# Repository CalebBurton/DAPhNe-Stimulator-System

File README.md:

## Digitally Adjustable Phrenic Nerve (DAPhNe) Stimulator System
### Northwestern University BME Senior Capstone Design (2016-2017)
#### Center for Autonomic Medicine in Pediatrics (CAMP) at Ann & Robert H. Lurie Children's Hospital of Chicago

<br></br>

Most recent documentation:

[**Digitally Adjustable Phrenic Nerve (DAPhNe) Stimulator - Getting Started, Rev 1.0**](https://github.com/AlexeyRevinski/DAPhNe-Stimulator-System/blob/master/Reference%20Documentation/DAPhNe_Getting_Started_v_1_0.pdf)

[**Digitally Adjustable Phrenic Nerve (DAPhNe) Stimulator - Technical Reference, Rev 1.1**](https://github.com/AlexeyRevinski/DAPhNe-Stimulator-System/blob/master/Reference%20Documentation/DAPhNe_Technical_Reference_v_1_1.pdf)

<br></br>

The focus of this project is the development and testing of a novel implantable phrenic nerve stimulator, to be used in patients with Congenital Central Hypoventilation Syndrome (CCHS) - specifically, children. The following sections summarize the project; to get to know the project in extensive detail, please refer to project documents under "Reference Documentation".

<br></br>

## Project Description
### Introduction to CCHS
Patients with CCHS have diminished autonomic nervous system function, which results in a variety of symptoms, the most prominent of which is insufficient ventilation. This results from poor phrenic nerve conduction; phrenic nerve is responsible for stimulating diaphragmatic contractions. While some patients are affected only mildly, some cannot breathe on their own, and require 24/7 ventilatory support.

### Current Solutions
This is usually done with a mechanical positive pressure ventilator; oxygenated air is forced into the patient's lungs by a mechanical piston. While this is a proven solution to the problem, these devices are enormous to carry around for small children; they are loud and extremely expensive. Patients also require a tracheotomy to be performed for this to work.

Another solution is to stimulate the phrenic nerve electrically. The only device that does this right now is the [**Mark IV stimulator**](http://www.averybiomedical.com/breathing-pacemakers/system-information/) from Avery Biomedical. It consists of an external transmitter that sends pulses inductively through tissue to a passive receiver that interfaces with an electrode in the vicinity of the nerve. This is the only solution on the market, and, while it has several advantages over the mechanical ventilator, it also has a variety of shortcomings that include:
 - Restricted mobility - antennae must be always attached to patient’s body for successful stimulation
 - System does not support multiple activity level settings, so each patient is forced to use two or three transmitters and mechanically switch between them each time the patient participates in a different activity (sleep vs. walk vs. run vs. eat, etc.)
 - Weight and size of the transmitter box - weight = 2 lb, volume = 511 cm3. A small child must carry this weight constantly
 - Unintuitive user interface - the device has non-linear, poorly labeled dials
 - Required presence of the external transmitter close to the patient's body restricts the patient's ability to participate in water-related activities.

### DAPhNe Stimulator System
The Digitally Adjustable Phrenic Nerve (DAPhNe) Stimulator System aims to lift those drawbacks and provide children with CCHS an implantable stimulator that would eliminate the need to be tethered to an external controller, allow for a variety of programmable settings to be switched "on the fly", and allow participation on water-related activities without fear of device malfunction or electric shock. 

The above objectives are accomplished by digitalization of the system, employing wireless charging, and wireless short range communication.  The DAPhNe stimulator is battery powered and charged inductively through skin; it provides constant stimulation to the nerve on its own without the need for an external inductive antenna. The external controller uses NFC technology to wirelessly transmit new activity level parameters to the implant, and the implant automatically adjusts its internal variables on the next breath. Thus, the patient is not tethered to anything, and the transition between various activity levels is seamless. Based on most recent power consumption testing and calculations, the device in its current state would be able to support the patient for one week on one battery charge, after which the battery is recharged wirelessly.

Currently, the DAPhNe Stimulator System consists of two custom-designed PCB prototype boards interfacing with some off-the-shelf components. This prototype was recently tested for equivalence against the Avery Biomedical Mark IV system in New Zealand white rabbits, and proved successful in stimulating the phrenic nerve effectively. The external user interface is being developed concurrently. 
<br></br>

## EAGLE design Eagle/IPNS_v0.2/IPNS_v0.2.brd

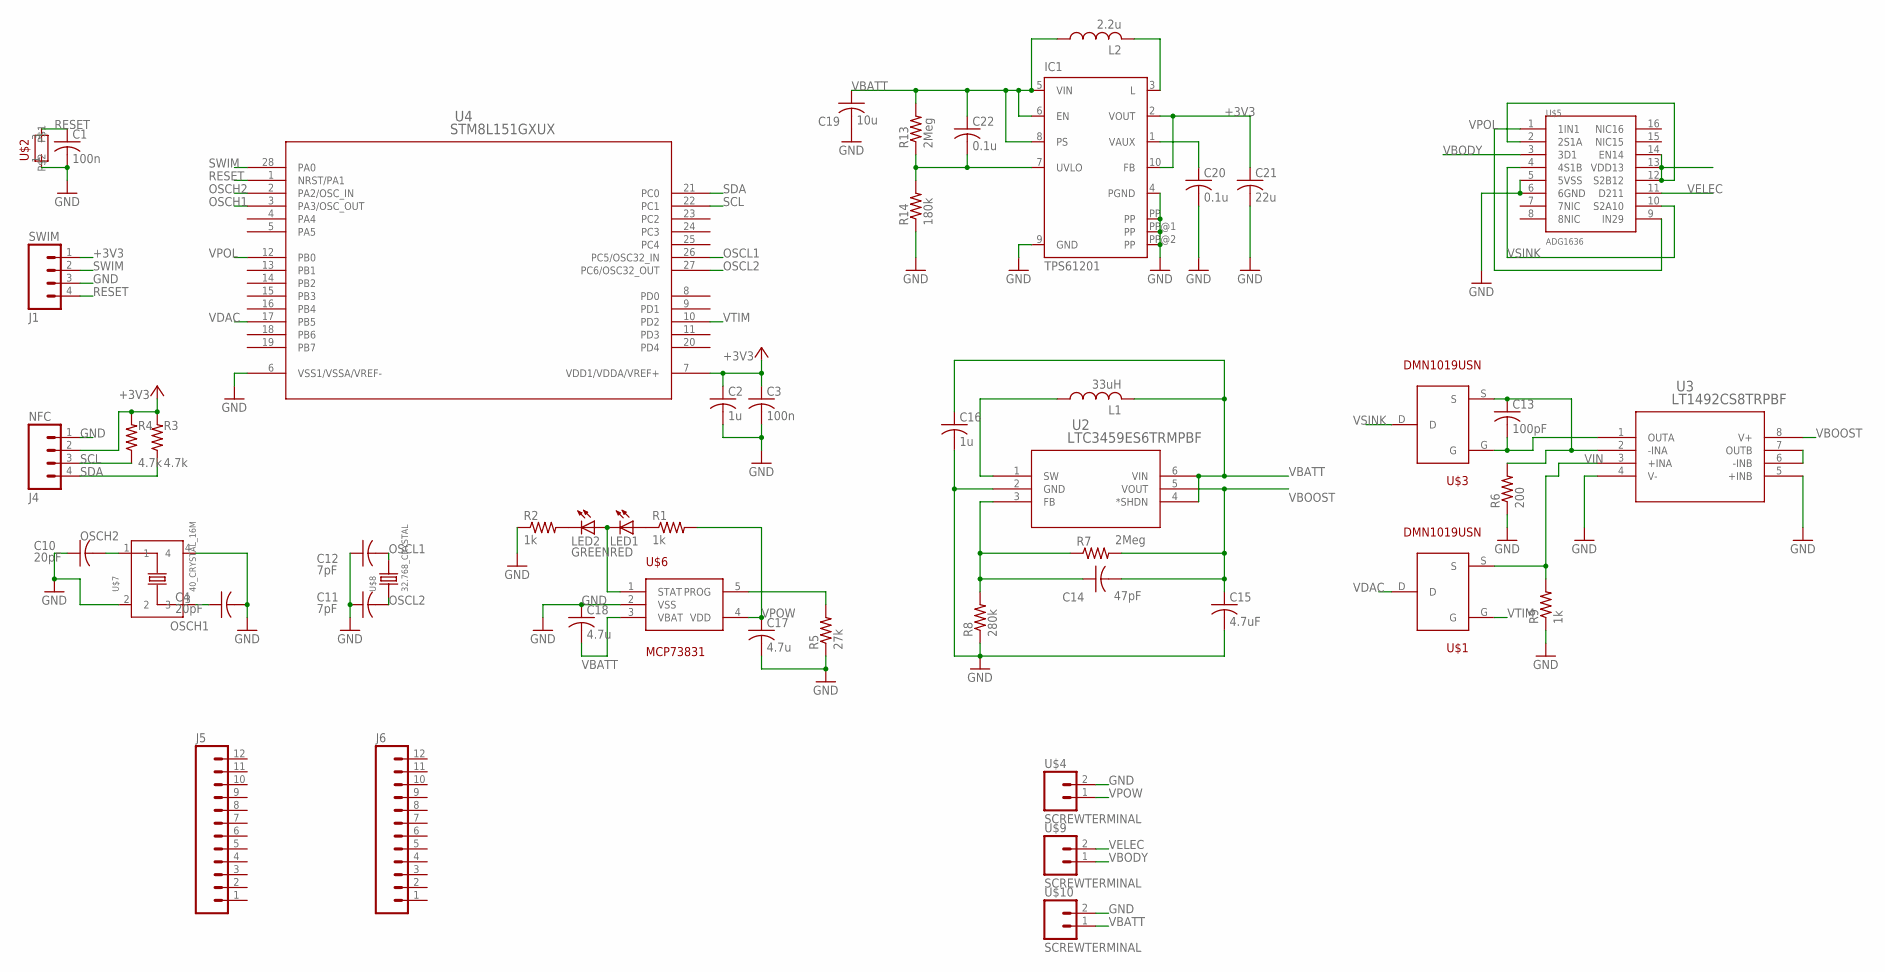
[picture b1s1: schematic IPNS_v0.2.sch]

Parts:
C1, C3: 100n; C0603
C2, C16: 1u; C0603
C4, C10: 20pF; C0603
C11, C12: 7pF; C0603
C13: 100pF; C0603
C14: 47pF; C0603
C15: 4.7uF; C0603
C17, C18: 4.7u; C0603
C19: 10u; C0603
C20, C22: 0.1u; C0603
C21: 22u; C0603
IC1: TPS61201; S-PDSO-N10
J1: SWIM; 1X04
J4: NFC; 1X04
J5, J6: M12PTH; 1X12
L1: 33uH; L2012C
L2: 2.2u; L2012C
LED1: RED; SML0603
LED2: GREEN; SML0603
R1, R2, R9: 1k; R0603
R3, R4: 4.7k; R0603
R5: 27k; R0603
R6: 200; R0603
R7, R13: 2Meg; R0603
R8: 280k; R0603
R14: 180k; R0603
U2: LTC3459ES6TRMPBF; TSOT-23_S6
U3: LT1492CS8TRPBF; SO-8_S
U4: STM8L151GXUX; UFQFPN-28
U$1, U$3: DMN1019USN
U$2: PUSH-BUTTON
U$4, U$9, U$10: SCREWTERMINAL
U$5: ADG1636; TSSOP16
U$6: MCP78381; SOT23-5L
U$7: 40_CRYSTAL_16M; X4-SMD-3.2X2.5X0.7MM
U$8: 32.768_CRYSTAL; X2-SMD-3.2X1.5X0.55MM

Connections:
+3V3: C2.1, C3.1, C21.1, IC1.2 (VOUT), IC1.10 (FB), J1.1, J4.2, R3.2, R4.2, U4.7 (VDD1/VDDA/VREF+)
GND: C1.2, C2.2, C3.2, C4.2, C10.1, C11.1, C12.1, C15.2, C16.2, C17.2, C18.1, C19.2, C20.2, C21.2, IC1.4 (PGND), IC1.9 (GND), IC1.PP, IC1.PP@1 (PP), IC1.PP@2 (PP), J1.3, J4.1, R2.1, R5.1, R6.1, R8.1, R9.1, R14.1, U2.2 (GND), U3.4 (V-), U3.5 (+INB), U4.6 (VSS1/VSSA/VREF-), U$2.1, U$4.2, U$5.5 (5VSS), U$5.6 (6GND), U$6.2 (VSS), U$7.2, U$7.4, U$10.2
unnamed: LED1.C, LED2.A, U$6.1 (STAT)
unnamed: C13.1, R6.2, U3.2 (-INA), U$3.S
unnamed: U3.6 (-INB), U3.7 (OUTB)
unnamed: C14.1, R7.1, R8.2, U2.3 (FB)
unnamed: L1.1, U2.1 (SW)
unnamed: LED2.C, R2.2
unnamed: LED1.A, R1.1
unnamed: C13.2, U3.1 (OUTA), U$3.G
unnamed: R5.2, U$6.5 (PROG)
unnamed: IC1.3 (L), L2.2
unnamed: C20.1, IC1.1 (VAUX)
unnamed: C22.2, IC1.7 (UVLO), R13.1, R14.2
unnamed: U$5.2 (2S1A), U$5.12 (S2B12), U$5.13 (VDD13), U$5.14 (EN14)
OSCH1: C4.1, U4.3 (PA3/OSC_OUT), U$7.3
OSCH2: C10.2, U4.2 (PA2/OSC_IN), U$7.1
OSCL1: C12.2, U4.26 (PC5/OSC32_IN), U$8.2
OSCL2: C11.2, U4.27 (PC6/OSC32_OUT), U$8.1
RESET: C1.1, J1.4, U4.1 (NRST/PA1), U$2.3
SCL: J4.3, R4.1, U4.22 (PC1)
SDA: J4.4, R3.1, U4.21 (PC0)
SWIM: J1.2, U4.28 (PA0)
VBATT: C16.1, C18.2, C19.1, C22.1, IC1.5 (VIN), IC1.6 (EN), IC1.8 (PS), L1.2, L2.1, R13.2, U2.4 (*SHDN), U2.6 (VIN), U$6.3 (VBAT), U$10.1
VBODY: U$5.3 (3D1), U$9.1
VBOOST: C14.2, C15.1, R7.2, U2.5 (VOUT), U3.8 (V+)
VDAC: U4.17 (PB5), U$1.D
VELEC: U$5.11 (D211), U$9.2
VIN: R9.2, U3.3 (+INA), U$1.S
VPOL: U4.12 (PB0), U$5.1 (1IN1), U$5.9 (IN29)
VPOW: C17.1, R1.2, U$4.1, U$6.4 (VDD)
VSINK: U$3.D, U$5.4 (4S1B), U$5.10 (S2A10)
VTIM: U4.10 (PD2), U$1.G

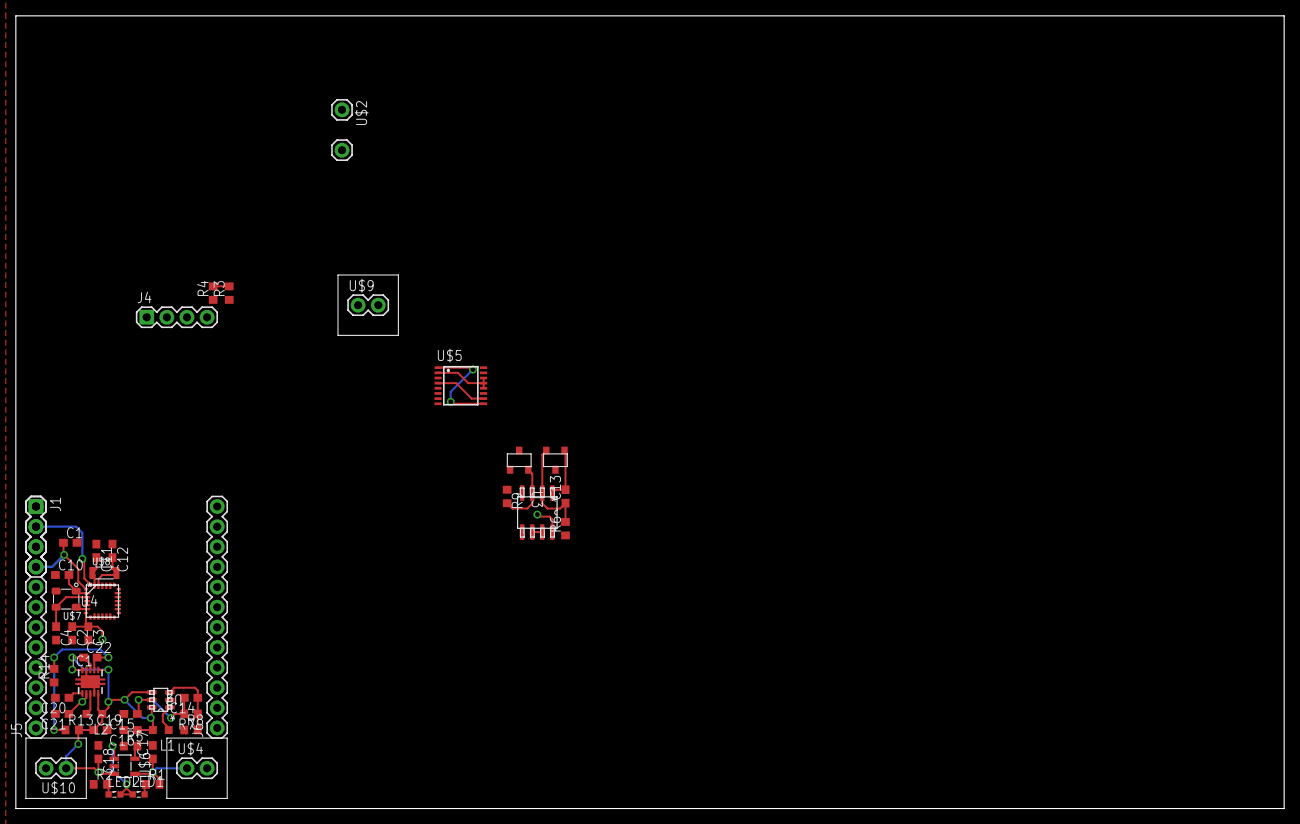
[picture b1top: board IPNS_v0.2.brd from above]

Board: 2 copper layers, 160.0 x 100.0 mm, 50 parts (0 on the bottom side), 33 nets.

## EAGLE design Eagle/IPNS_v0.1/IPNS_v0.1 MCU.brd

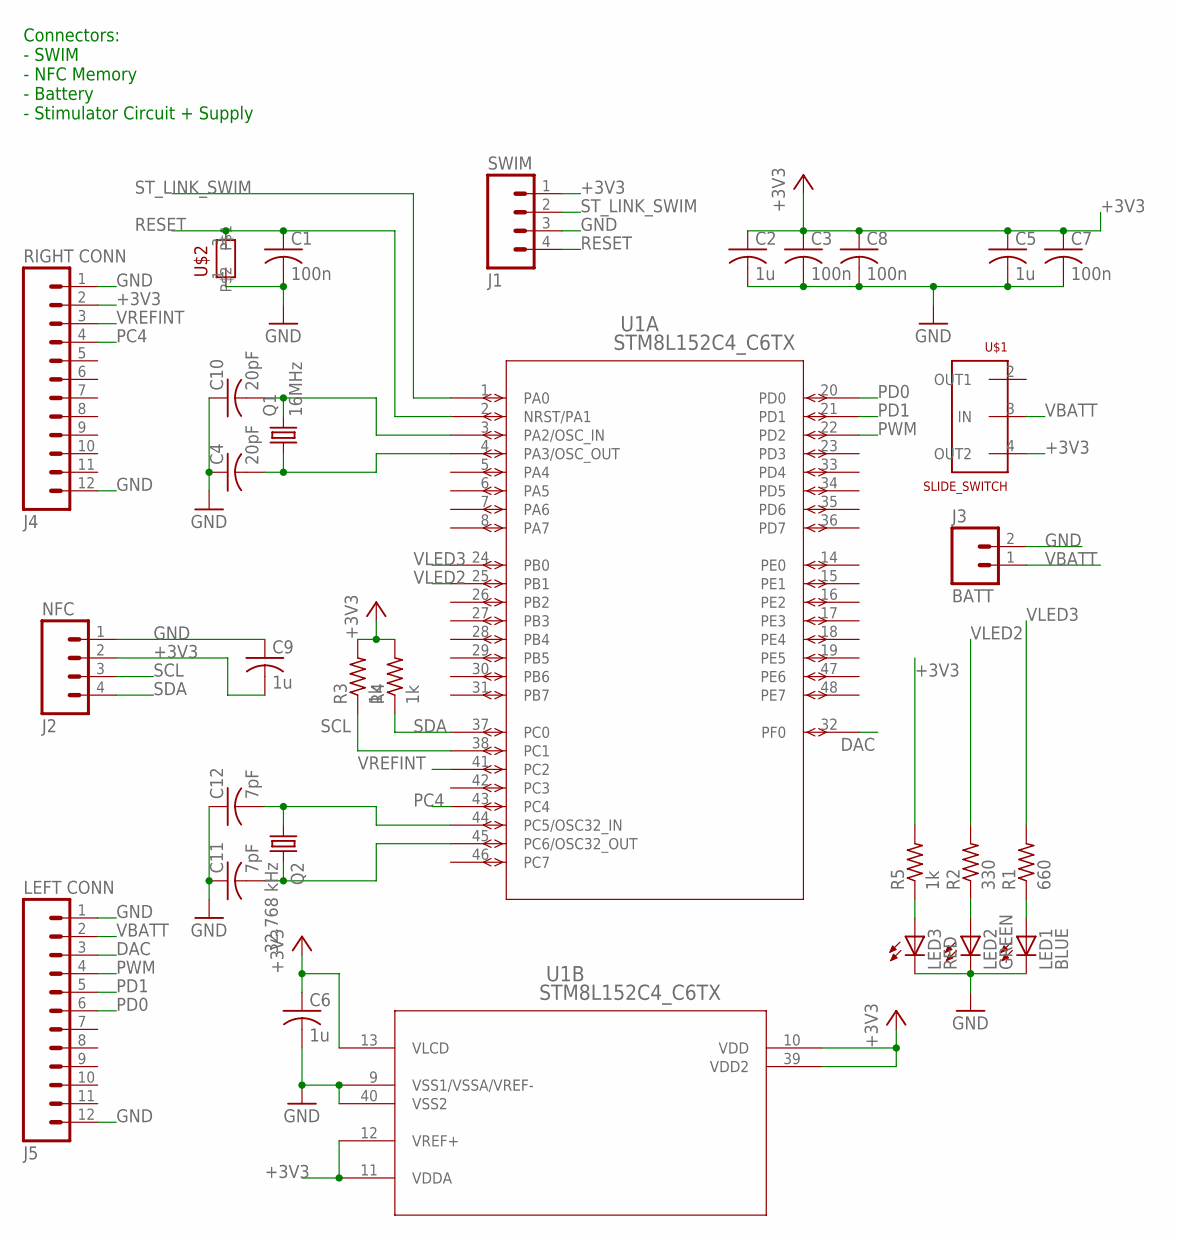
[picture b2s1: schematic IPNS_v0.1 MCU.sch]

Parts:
C1, C3, C7, C8: 100n; C0805
C2, C5, C6, C9: 1u; C0805
C4, C10: 20pF; C0805
C11, C12: 7pF; C0805
J1: SWIM; 1X04
J2: NFC; 1X04
J3: BATT; 1X02
J4: RIGHT CONN; 1X12
J5: LEFT CONN; 1X12
LED1: BLUE; CHIP-LED0805
LED2: GREEN; CHIP-LED0805
LED3: RED; CHIP-LED0805
Q1: 16MHz; HC49/S
Q2: 32.768 kHz; TC26H
R1: 660; R0805
R2: 330; R0805
R3, R4, R5: 1k; R0805
U1: STM8L152C4_C6TX; LQFP48-7X7MM
U$1: SLIDE_SWITCH
U$2: PUSH-BUTTON

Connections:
+3V3: C2.1, C3.1, C5.1, C6.1, C7.1, C8.1, C9.2, J1.1, J2.2, J4.2, R3.2, R4.2, R5.2, U1.10 (VDD), U1.11 (VDDA), U1.12 (VREF+), U1.13 (VLCD), U1.39 (VDD2), U$1.4 (OUT2)
DAC: J5.3, U1.32 (PF0)
GND: C1.2, C2.2, C3.2, C4.1, C5.2, C6.2, C7.2, C8.2, C9.1, C10.1, C11.1, C12.1, J1.3, J2.1, J3.2, J4.1, J4.12, J5.1, J5.12, LED1.C, LED2.C, LED3.C, U1.9 (VSS1/VSSA/VREF-), U1.40 (VSS2), U$2.1
unnamed: C10.2, Q1.2, U1.3 (PA2/OSC_IN)
unnamed: C11.2, Q2.2, U1.45 (PC6/OSC32_OUT)
unnamed: C4.2, Q1.1, U1.4 (PA3/OSC_OUT)
unnamed: C12.2, Q2.1, U1.44 (PC5/OSC32_IN)
unnamed: LED3.A, R5.1
unnamed: LED2.A, R2.1
unnamed: LED1.A, R1.1
PC4: J4.4, U1.43 (PC4)
PD0: J5.6, U1.20 (PD0)
PD1: J5.5, U1.21 (PD1)
PWM: J5.4, U1.22 (PD2)
RESET: C1.1, J1.4, U1.2 (NRST/PA1), U$2.3
SCL: J2.3, R3.1, U1.38 (PC1)
SDA: J2.4, R4.1, U1.37 (PC0)
ST_LINK_SWIM: J1.2, U1.1 (PA0)
VBATT: J3.1, J5.2, U$1.3 (IN)
VLED2: R2.2, U1.25 (PB1)
VLED3: R1.2, U1.24 (PB0)
VREFINT: J4.3, U1.41 (PC2)

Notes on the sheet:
Connectors: - SWIM - NFC Memory - Battery - Stimulator Circuit + Supply

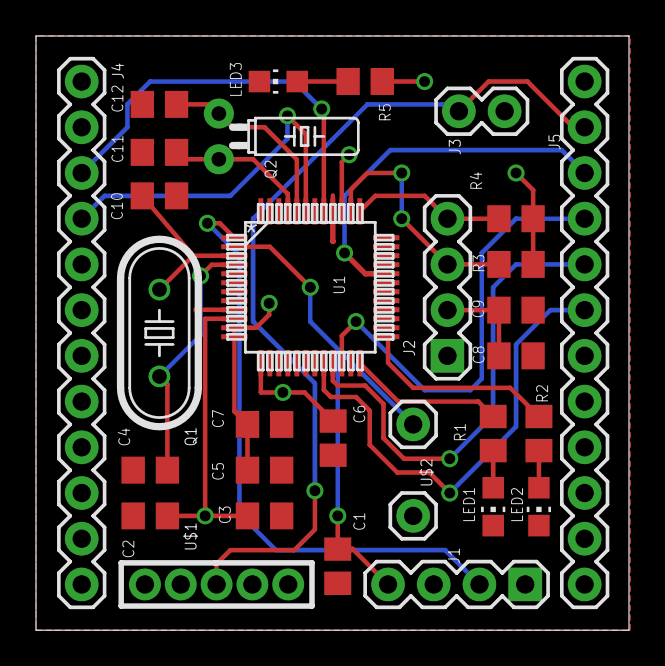
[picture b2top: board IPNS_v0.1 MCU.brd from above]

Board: 2 copper layers, 32.9 x 33.0 mm, 30 parts (0 on the bottom side), 22 nets.

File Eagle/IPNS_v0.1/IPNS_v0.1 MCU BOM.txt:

Partlist exported from C:/Users/Alexey Revinski/Documents/1_CLASS/BME 390-2/Repo/BME390/Eagle/IPNS_v0.1/IPNS_v0.1 MCU.sch at 2/9/2017 6:30 PM

Part Value           Device          Package      Description                          COPYRIGHT                                                   MANUFACTURER_PART_NUMBER MF MPN OC_FARNELL OC_NEWARK PROD_ID    VENDOR             
C1   100n            C-USC0805       C0805        CAPACITOR, American symbol                                                                                                                                                          
C2   1u              C-USC0805       C0805        CAPACITOR, American symbol                                                                                                                                                          
C3   100n            C-USC0805       C0805        CAPACITOR, American symbol                                                                                                                                                          
C4   20pF            C-USC0805       C0805        CAPACITOR, American symbol                                                                                                                                                          
C5   1u              C-USC0805       C0805        CAPACITOR, American symbol                                                                                                                                                          
C6   1u              C-USC0805       C0805        CAPACITOR, American symbol                                                                                                                                                          
C7   100n            C-USC0805       C0805        CAPACITOR, American symbol                                                                                                                                                          
C8   100n            C-USC0805       C0805        CAPACITOR, American symbol                                                                                                                                                          
C9   1u              C-USC0805       C0805        CAPACITOR, American symbol                                                                                                                                                          
C10  20pF            C-USC0805       C0805        CAPACITOR, American symbol                                                                                                                                                          
C11  7pF             C-USC0805       C0805        CAPACITOR, American symbol                                                                                                                                                          
C12  7pF             C-USC0805       C0805        CAPACITOR, American symbol                                                                                                                                                          
J1   SWIM            M04PTH          1X04         Header 4                                                                                                                                              CONN-09696                    
J2   NFC             M04PTH          1X04         Header 4                                                                                                                                              CONN-09696                    
J3   BATT            M02PTH          1X02         Standard 2-pin 0.1" header. Use with                                                                                                                                                
J4   RIGHT CONN      M12PTH          1X12         Header 12                                                                                                                                                                           
J5   LEFT CONN       M12PTH          1X12         Header 12                                                                                                                                                                           
LED1 BLUE            LEDCHIP-LED0805 CHIP-LED0805 LED                                                                                                                                                                                 
LED2 GREEN           LEDCHIP-LED0805 CHIP-LED0805 LED                                                                                                                                                                                 
LED3 RED             LEDCHIP-LED0805 CHIP-LED0805 LED                                                                                                                                                                                 
Q1   16MHz           CRYSTALHC49S    HC49/S       CRYSTAL                                                                                                                          1667008    unknown                                 
Q2   32.768 kHz      CRYSTALTC26H    TC26H        CRYSTAL                                                                                                                          unknown    unknown                                 
R1   660             R-US_R0805      R0805        RESISTOR, American symbol                                                                                                                                                           
R2   330             R-US_R0805      R0805        RESISTOR, American symbol                                                                                                                                                           
R3   1k              R-US_R0805      R0805        RESISTOR, American symbol                                                                                                                                                           
R4   1k              R-US_R0805      R0805        RESISTOR, American symbol                                                                                                                                                           
R5   220             R-US_R0805      R0805        RESISTOR, American symbol                                                                                                                                                           
U$1  SLIDE_SWITCH    SLIDE_SWITCH    SLIDE_SWITCH                                                                                                                                                                                     
U$2  PUSH-BUTTON     PUSH-BUTTON     PUSH-BUTTON                                                                                                                                                                                      
U1   STM8L152C4_C6TX STM8L152C4_C6TX LQFP48-7X7MM                                      Copyright (C) 2016 Accelerated Designs. All rights reserved stm8l152c4_c6tx                                                 ST Microelectronics

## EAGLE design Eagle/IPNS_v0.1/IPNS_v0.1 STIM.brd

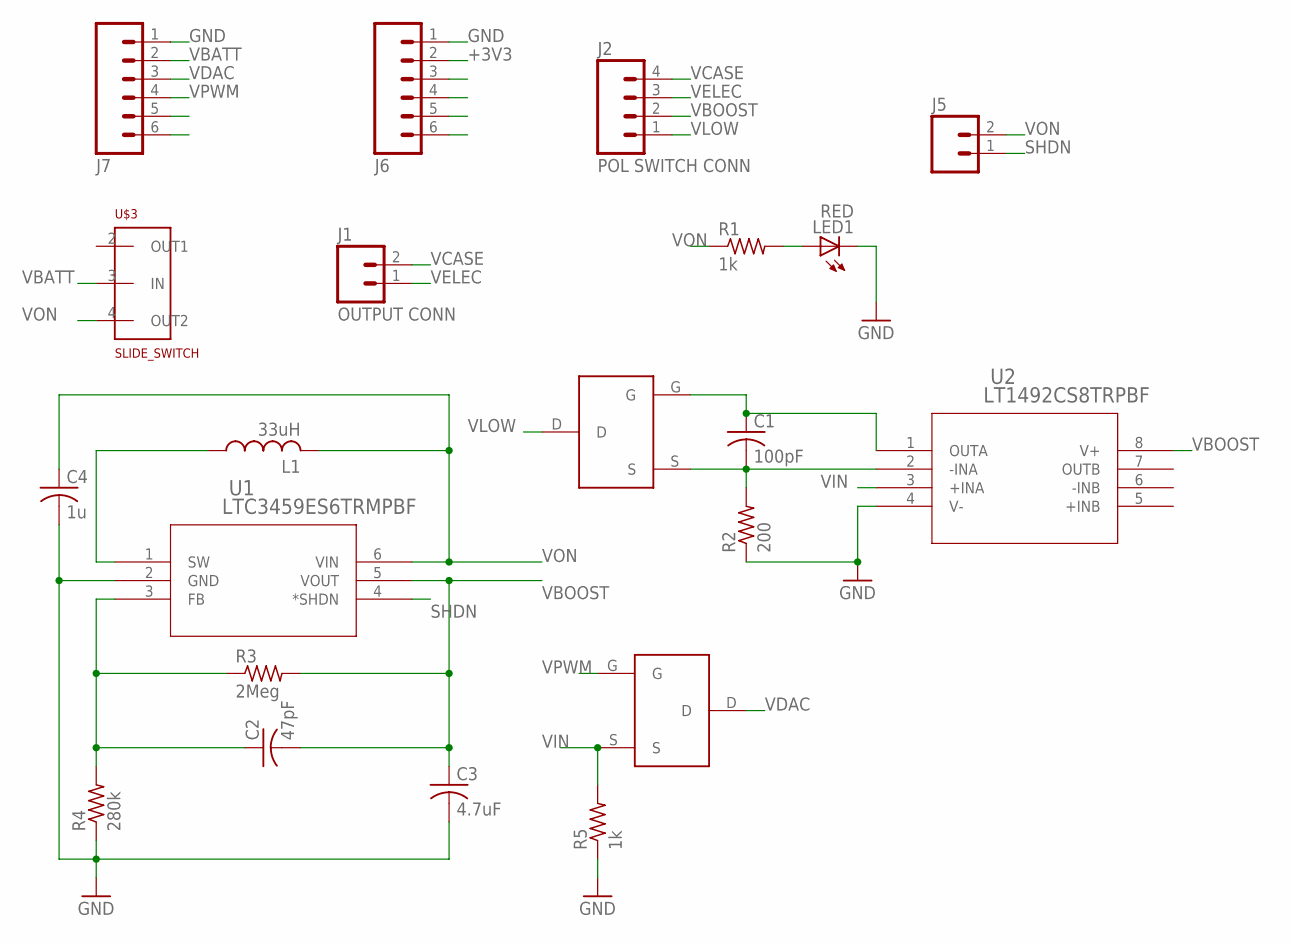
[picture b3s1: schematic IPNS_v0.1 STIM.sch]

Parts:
C1: 100pF; C0805
C2: 47pF; C0805
C3: 4.7uF; C0805
C4: 1u; C0805
J1: OUTPUT CONN; 1X02
J2: POL SWITCH CONN; 1X04
J5: M02PTH; 1X02
J6, J7: M06SILK_FEMALE_PTH; 1X06
L1: 33uH; L2012C
LED1: RED; CHIP-LED0805
R1: 1k; M0805
R2: 200; R0805
R3: 2Meg; R0805
R4: 280k; R0805
R5: 1k; R0805
U1: LTC3459ES6TRMPBF; TSOT-23_S6
U2: LT1492CS8TRPBF; SO-8_S
U$1, U$2: DMN1019USN
U$3: SLIDE_SWITCH

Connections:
+3V3: J6.2
GND: C3.2, C4.2, J6.1, J7.1, LED1.C, R2.1, R4.1, R5.1, U1.2 (GND), U2.4 (V-)
unnamed: LED1.A, R1.2
unnamed: C1.1, U2.1 (OUTA), U$1.G
unnamed: C1.2, R2.2, U2.2 (-INA), U$1.S
unnamed: C2.1, R3.1, R4.2, U1.3 (FB)
unnamed: L1.1, U1.1 (SW)
SHDN: J5.1, U1.4 (*SHDN)
VBATT: J7.2, U$3.3 (IN)
VBOOST: C2.2, C3.1, J2.2, R3.2, U1.5 (VOUT), U2.8 (V+)
VCASE: J1.2, J2.4
VDAC: J7.3, U$2.D
VELEC: J1.1, J2.3
VIN: R5.2, U2.3 (+INA), U$2.S
VLOW: J2.1, U$1.D
VON: C4.1, J5.2, L1.2, R1.1, U1.6 (VIN), U$3.4 (OUT2)
VPWM: J7.4, U$2.G

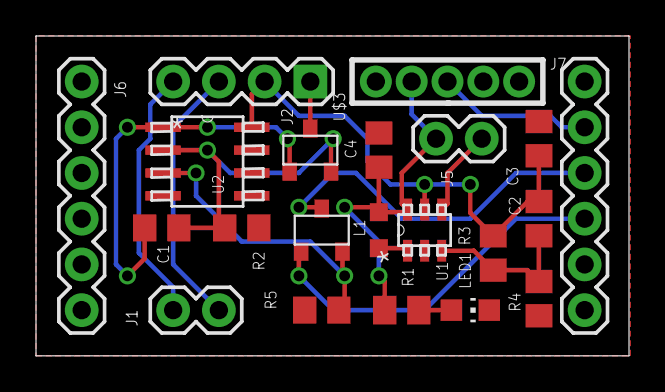
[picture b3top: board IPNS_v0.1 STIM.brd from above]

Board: 2 copper layers, 32.9 x 17.8 mm, 21 parts (0 on the bottom side), 16 nets.

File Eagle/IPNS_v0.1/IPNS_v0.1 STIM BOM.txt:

Partlist exported from C:/Users/Alexey Revinski/Documents/1_CLASS/BME 390-2/Repo/BME390/Eagle/IPNS_v0.1/IPNS_v0.1 STIM.sch at 2/9/2017 6:31 PM

Part Value            Device             Package      Description                          COPYRIGHT                                                   MANUFACTURER_PART_NUMBER PROD_ID    VENDOR           
C1   100pF            C-USC0805          C0805        CAPACITOR, American symbol                                                                                                                            
C2   47pF             C-USC0805          C0805        CAPACITOR, American symbol                                                                                                                            
C3   4.7uF            C-USC0805          C0805        CAPACITOR, American symbol                                                                                                                            
C4   1u               C-USC0805          C0805        CAPACITOR, American symbol                                                                                                                            
J1   OUTPUT CONN      M02PTH             1X02         Standard 2-pin 0.1" header. Use with                                                                                                                  
J2   POL SWITCH CONN  M04PTH             1X04         Header 4                                                                                                                  CONN-09696                  
J5                    M02PTH             1X02         Standard 2-pin 0.1" header. Use with                                                                                                                  
J6                    M06SILK_FEMALE_PTH 1X06         Header 6                                                                                                                  CONN-08437                  
J7                    M06SILK_FEMALE_PTH 1X06         Header 6                                                                                                                  CONN-08437                  
L1   33uH             L-USL2012C         L2012C       INDUCTOR, American symbol                                                                                                                             
LED1 RED              LEDCHIP-LED0805    CHIP-LED0805 LED                                                                                                                                                   
R1   1k               R-US_M0805         M0805        RESISTOR, American symbol                                                                                                                             
R2   200              R-US_R0805         R0805        RESISTOR, American symbol                                                                                                                             
R3   2Meg             R-US_R0805         R0805        RESISTOR, American symbol                                                                                                                             
R4   280k             R-US_R0805         R0805        RESISTOR, American symbol                                                                                                                             
R5   1k               R-US_R0805         R0805        RESISTOR, American symbol                                                                                                                             
U$1  DMN1019USN       DMN1019USN         DMN1019USN                                                                                                                                                         
U$2  DMN1019USN       DMN1019USN         DMN1019USN                                                                                                                                                         
U$3  SLIDE_SWITCH     SLIDE_SWITCH       SLIDE_SWITCH                                                                                                                                                       
U1   LTC3459ES6TRMPBF LTC3459ES6TRMPBF   TSOT-23_S6                                        Copyright (C) 2016 Accelerated Designs. All rights reserved ltc3459es6#trmpbf                   Linear Technology
U2   LT1492CS8TRPBF   LT1492CS8TRPBF     SO-8_S                                                                                                        lt1492cs8#trpbf                     Linear Technology

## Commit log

2016-11-05 :octocat: Added .gitattributes & .gitignore files
2016-11-05 Started Implant STM8L Project
2016-11-05 Cleaning up the code
2016-11-05 Code is cleaned up. On to switching TIM2 functionality to PWM
2016-11-05 Revert "Started Implant STM8L Project"
    This reverts commit eefdeab2b19860805d8697df93142ee78f087b58.
    # Conflicts:
    # Implant STM8L Program/Project/EWSTM8/Debug/Exe/project.out
    # Implant STM8L Program/Project/EWSTM8/Debug/Obj/main.o
    # Implant STM8L Program/Project/EWSTM8/Debug/Obj/main.pbi
    # Implant STM8L Program/Project/EWSTM8/Debug/Obj/main.pbi.cout
2016-11-05 Reverted back to original program
2016-11-05 Changed private functions a bit
2016-11-05 Finished main for now
2016-11-05 Code almost cleaned up
2016-11-05 Code is cleaned up. On to PWM
2016-11-05 Code working again.
2016-11-05 Improving pulse generation architecture
2016-11-05 Able to change Inspiration to Expiration ratio
2016-11-06 Generating pulses based on BPM and I:E ratio
2016-11-06 PWM functionality achieved.
    Pulses can be varied by:
    - pulse width
    - pulse frequency
    - breaths/min
    - inspiration : total cycle ratio
2016-11-06 Cleaned up code (PWM implemented)
2016-11-20 Controls: p-width, p-freq, bpm, i:e ratio
2016-11-20 DAC implemented
2016-11-20 Cleaned up code; DAC implemented
2016-11-20 Cleaned up code
2016-11-20 Cleaned code more
2016-11-20 Cleaned code even more
2016-11-26 Started NFC program based on STSW-M24LR016 library
2016-11-26 Threw out unnecessary stuff
2016-11-28 Started Pulse+NFC program
2016-12-12 Set up everything on new computer
2016-12-15 Set everything up for current-controller stimulation
2016-12-15 Deleted erroneous project
2016-12-15 Renamed package, imported pulse generator program into NFC+Pulse package
2016-12-15 DeInitClock() function from NFC firmware works
2016-12-15 GPIO config function from NFC Program works
2016-12-15 Debugging I2C communication
2016-12-16 Successfully reading message from NFC tag
2016-12-16 WIRELESS PULSE CONTROL ACHIEVED! One way only so far.
2016-12-16 Control refined; imput standardized and bugs fixed (on this standard input)
2016-12-16 Code cleaned up
2016-12-18 Stack overflow issue fixed
2017-01-06 NFC message error check partially implemented
2017-01-15 LTSpice Simulation Started
2017-01-15 Outputting 5mA max using 10V source, and 1.5k/1pF tissue
2017-01-17 Actual 3.7-10V boost converter implemented
2017-01-17 Deleted the net file
2017-01-17 Deleted fft file
2017-01-24 Reverted multiple commits... file problems. NET, RAW, and OP.RAW not included.
    Revert "Actual 3.7-10V boost converter implemented"
    This reverts commit
    f67e475714b58a91e96f6e9034a94f1b604d0d0d.
    Merge branch 'master' of https://github.com/AlexeyRevinski/BME390
    FIle problems
    Revert "Fixed simulation file size problem"
2017-01-28 Started an EagleCAD schematic
2017-01-28 Imported STM8L microcontroller
2017-01-28 Eagle library created
2017-01-28 Powering up microcontroller
2017-01-28 Microcontroller setup possibly finished with minor unknowns
2017-01-28 Various connectors implemented: SWIM , battery supply board, and NFC memory connector
2017-01-28 The physical board started
2017-01-28 Physical board semi-rearranged
2017-01-28 All connections wired except for STM8L breakout pins
2017-01-28 Routed Vbatt, Vmcu (3.3V), GND, and PWM and DAC to breakout pins
2017-01-28 Fixed clearances. ERC = no errors, DRC = only stop mask errors
2017-01-28 Board and schematic overall finished for MCU module. Need to check RC values
2017-01-29 Changed bottom text
2017-01-29 Deleted autorouter file
2017-01-29 Resized ground polygon
2017-01-29 Deleted some silkscreen
2017-01-29 Moved legacy IAR projects into one folder
2017-01-29 Deleted some more silkscreen
2017-01-30 Made names font smaller; renumbered parts
2017-01-30 Renamed board/schematic file; moved the button location a bit
2017-01-30 Started stimulation module board
2017-01-30 Changed mosfet components and decreased load to 1.1k
2017-01-30 Developed a CAD model for the mosfet part
2017-01-31 Positioned components for STIM board
2017-01-31 Routed everything; no DRC errors other than Stop Mask
2017-02-05 Broke out more pins on the MCU module
2017-02-06 Two PCBs clearances adjusted
2017-02-06 Adjusted silkscreen on both PCBs; trace width/clearances checks
2017-02-06 Added README.md
2017-02-06 Deleted some non-belonging files
2017-02-06 Moved reference documentation to git folder
2017-02-06 Moved some component models into reference documentation folder
2017-02-06 Deleting simulation binary files
2017-02-06 Generated gerber files for PCB manufacturing
2017-02-07 Updated links in README.md
2017-02-07 Elaborated on hardware checklist
2017-02-07 Elaborated on Software Checklist
2017-02-07 Formatted README.md
2017-02-07 Updated Quick Start intro in README.md
2017-02-08 Moved some components on STIM and updated Gerber files
2017-02-08 Changed a capacitor value for body model in LTSPice
2017-02-08 Grammar fixes...
2017-02-14 Developed biphasic stim signal
    TIM1 is used for logic (short pulse, break, long pulse, break - all
    within a set selectable time period (for now, hardcoded at 50ms -
    20Hz)). DAC is used for pulse amplitude - high (~1V) during short pulse,
    then switch to low (~0.1V) during break, keep low for long pulse, then
    switch to high during break. This way, the circuit output is large short
    pulse, break, then small long pulse, break. Need to implement the SPDT
2017-02-14 Added some screenshots of biphasic timing/DAC program
2017-02-15 Biphasic got three controls (including polarity)
    TIM2 is coupled to TIM1 now. TIM2 outputs a logic signal for switching
    polarity of the electrode wrt case based on TIM1 timings. TIM2 DMA
    requests update TIM2's OC1 register; when a switch is desired, set OC1
    to be low (~10-20 to carry over the TIM1 pulse and allow the physical
    pulse to die before switching); when no switch is desired, set OC1 to
    0xFFFF. In current configuration, polarity switches 50us after the each
2017-02-15 Minor changes
2017-02-15 Renamed folder; changed gitignore
2017-03-02 Combined 3-signal control with NFC and RTC wake up
2017-03-08 Got NFC to work with 3-control system
2017-03-10 Visuals folder updated
2017-04-03 Started IPNS_v0.2
2017-04-12 Fixed polarity switching inversion + initialization problems
2017-04-16 Developed IPNS_v0.2 further
2017-04-19 Updated IPNS_v0.2
2017-04-30 Cleaned up the project
    Moved M24LR04 files into their own driver folder. Deleted unused
    constants, function prototypes, etc. Moved hardware-related functions,
    constants, etc. into separate C and H files.
2017-04-30 Cleaned up main, redefined state structure
2017-04-30 Broke up "private_functions" further
2017-05-02 Reorganized code; fixed signal discrepancy problems
    Able to use NFC to change pulse width, pulse amplitude, breathing rate,
    inspiratory time. Interpulse interval will be implemented next
2017-05-02 Interpulse interval NFC implemented
    Output is correct up to 80.5 ms interpulse interval. After this value,
    for some reason, pulses start inverting relative to previous pulses (one
    normal , one inverted, one normal, etc)
2017-05-02 Fixed timing issue in phase 4
2017-05-08 Lots of reference documentation provided
2017-05-16 Commented Code
2017-06-06 Uploaded visuals and receiver holder CAD
2017-06-06 Uploaded correct version of final report
2017-06-06 Uploaded first report
2017-06-06 Rotated STIM picture
2017-06-06 Updated prototype image
2017-06-06 Added a picture collage
2017-08-09 Committing changes made during animal experiment
2017-09-10 Minor formatting
2017-09-10 Renamed parent directory for the MCU project
2017-09-10 Added copyright notice; minor formatting; removed vestigial code
2017-09-10 Added copyright to all files
2017-09-18 Deleted legacy code and cleaned project output files
2017-09-18 Added space to break up preamble
2017-09-18 Updated the Overall Circuit Diagram
2017-09-18 Commit "Updated circuit diagram"
2017-09-18 Last commit before pass-off (hopefully...)
2017-09-18 Last commit before pass-off
    Eagle run-time file changed
2017-10-21 Initial fork
    Initial fork of Alexey's code
2017-11-15 Changing test parameters

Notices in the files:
parts and their libraries:
COPYRIGHT: Copyright (C) 2016 Accelerated Designs. All rights reserved
